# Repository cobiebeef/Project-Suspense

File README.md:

# Project-Suspense
SDP 23/24 Files

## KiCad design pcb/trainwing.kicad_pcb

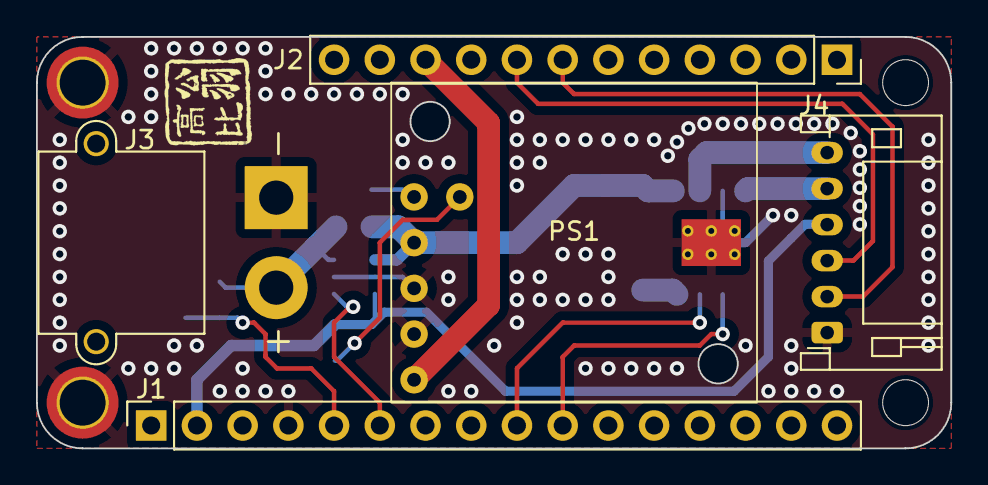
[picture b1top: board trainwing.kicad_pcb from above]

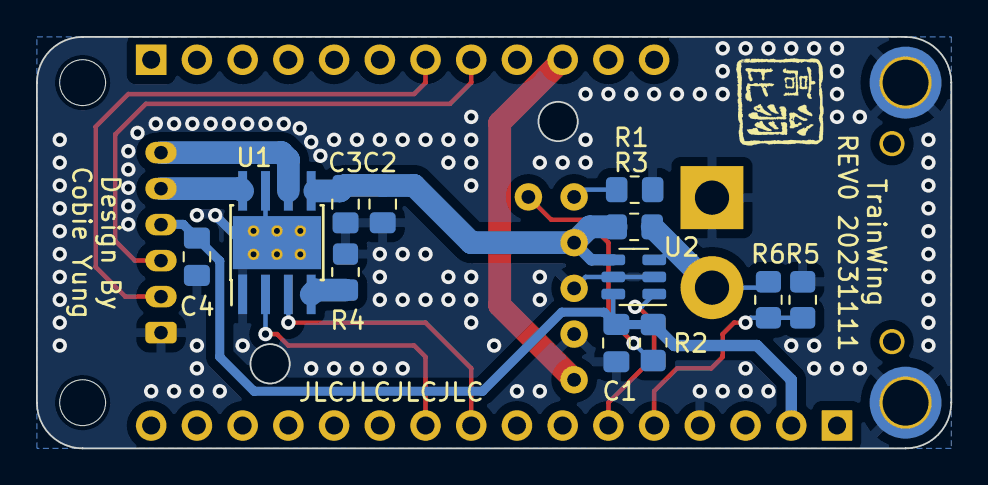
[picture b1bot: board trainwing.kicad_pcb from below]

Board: 2 copper layers, 50.8 x 22.9 mm, 21 parts (12 on the bottom side), 16 nets.

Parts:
C1, C2, C3, C4: C; C_0805_2012Metric_Pad1.18x1.45mm_HandSolder
H1, H3: MountingHole; MountingHole_2.55mm
H2, H4: MountingHole_Pad; MountingHole_2.55mm_Pad_TopBottom
J1: Conn_01x16_Socket; PinSocket_1x16_P2.54mm_Vertical
J2: Conn_01x12_Socket; PinSocket_1x12_P2.54mm_Vertical
J3: Conn_01x02_Socket; AMASS_XT30PW-M_1x02_P2.50mm_Horizontal
J4: Conn_01x06; JST_PH_S6B-PH-K_1x06_P2.00mm_Horizontal
PS1: D30V30F5
R1, R2, R4, R5, R6: R_US; R_0805_2012Metric_Pad1.20x1.40mm_HandSolder
R3: R_Small_US; R_0805_2012Metric_Pad1.20x1.40mm_HandSolder
U1: DRV8871DDA; Texas_HTSOP-8-1EP_3.9x4.9mm_P1.27mm_EP2.95x4.9mm_Mask2.4x3.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
U2: INA181; SOT-23-6

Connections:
+3V3: C1.1, C4.2, J1.2, J4.4, R2.2, U2.6 (V+)
+5V: J2.10, PS1.6 (VOUT)
+BATT: J3.2, R3.1, R6.1, U2.3 (+)
+VM: C2.2, C3.2, PS1.3 (VIN), R3.2, U1.5 (VM), U2.4 (-)
/A0: J1.5, R5.1, R6.2
/A1: J1.6, U2.1
/A4_D24: J1.9, U1.3 (IN1)
/A5_D25: J1.10, U1.2 (IN2)
/D11: J2.7, J4.2
/D12: J2.8, J4.3
/MD1: J4.6, U1.6 (OUT1)
/MD2: J4.5, U1.8 (OUT2)
GNDREF: C1.2, C2.1, C3.1, C4.1, H2.1, H4.1, J1.4, J3.1, J4.1, PS1.4 (GND), R1.2, R4.2, R5.2, U1.1 (GND), U1.7 (GND), U1.9 (GND), U2.2 (GND), U2.5 (REF)
unnamed: PS1.2 (EN), R1.1
unnamed: PS1.1 (PG), R2.1
unnamed: R4.1, U1.4 (ILIM)

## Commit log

2024-04-24 Add files via upload
    First Commit, added controller code
2024-04-24 Added PCB Files
2024-04-24 Rename sdp_demo_v1_2.ino to code/sdp_demo_v1_2.ino
2024-04-24 Rename trainwing.kicad_pro to pcb/trainwing.kicad_pro
